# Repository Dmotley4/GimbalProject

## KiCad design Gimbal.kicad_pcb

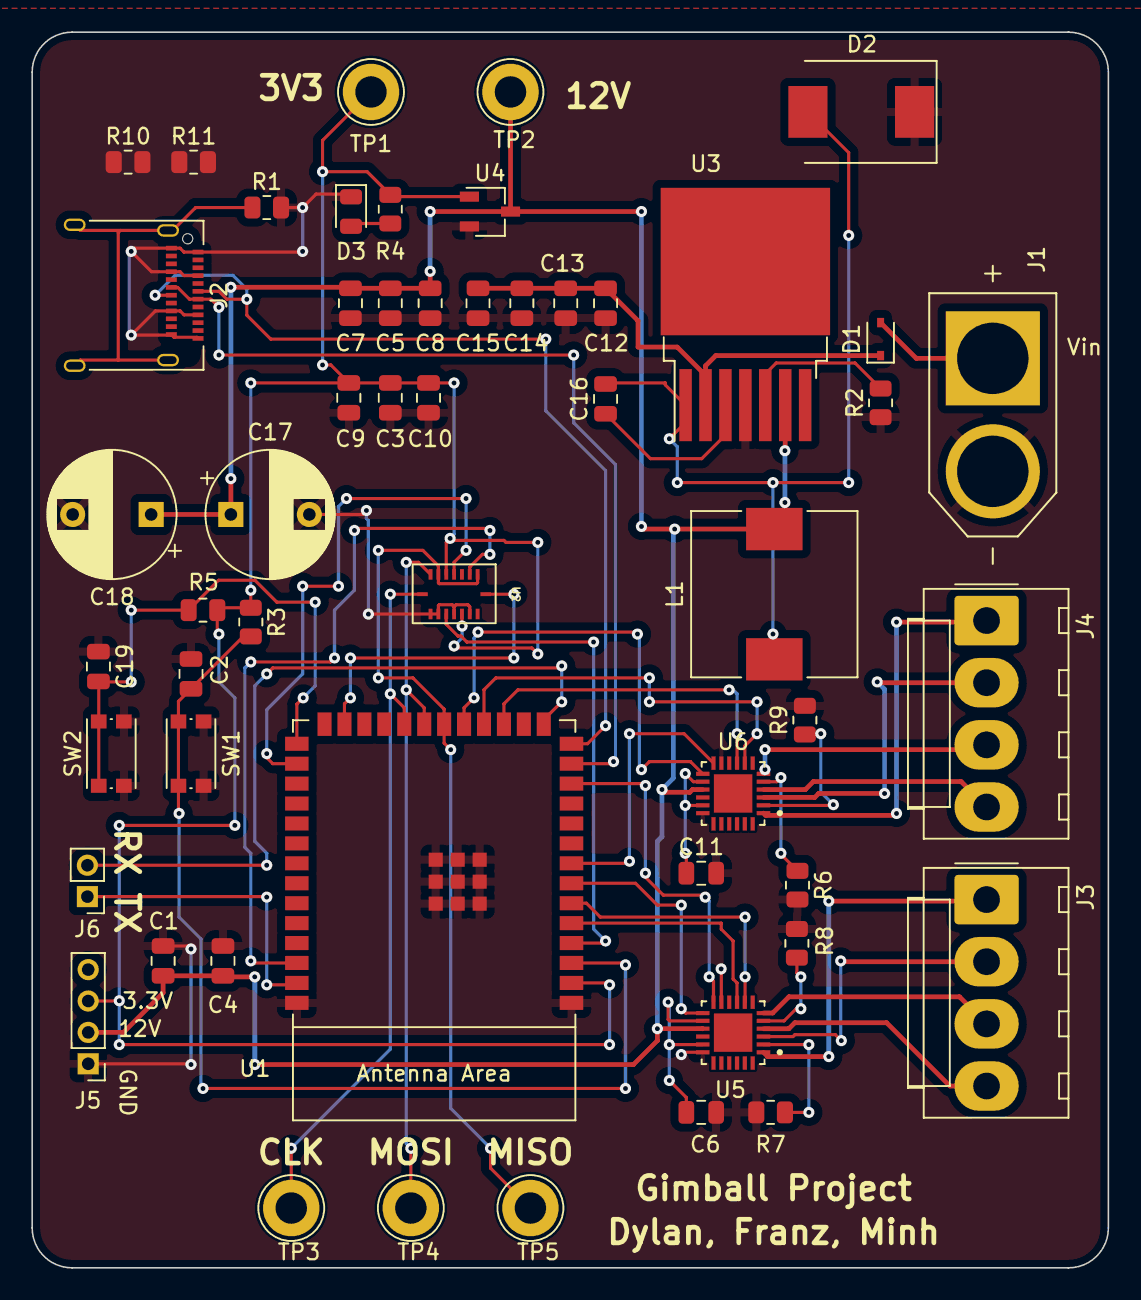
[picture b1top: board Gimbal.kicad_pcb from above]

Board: 2 copper layers, 68.6 x 78.7 mm, 53 parts (0 on the bottom side), 45 nets.

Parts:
C1, C6, C11: 22uF; C_0805_2012Metric
C2, C5, C8, C19: 0.1uF; C_0805_2012Metric
C3: 1uF; C_0805_2012Metric
C4, C7: 10uF; C_0805_2012Metric
C9, C10: 100nF; C_0805_2012Metric
C12, C13, C14: 15uF; C_0805_2012Metric
C15: 0.47 uF; C_0805_2012Metric
C16: .01uF; C_0805_2012Metric
C17, C18: 180uF; CP_Radial_D8.0mm_P5.00mm
D1: D_Schottky; D_SOD-323
D2: DIODE; D_SMC
D3: LED; LED_0805_2012Metric
J1: XT60-M; AMASS_XT60-M
J2: USB_C_Receptacle_USB2.0; USB_C_Receptacle_Amphenol_12401610E4-2A
J3, J4: 0022232041; Molex_KK-396_A-41791-0004_1x04_P3.96mm_Vertical
J5: 0022232041; PinHeader_1x04_P2.00mm_Vertical
J6: Conn_01x02; PinHeader_1x02_P2.00mm_Vertical
L1: 22uH; L_10.4x10.4_H4.8
R1, R4: 100; R_0805_2012Metric
R2: 5.6k; R_0805_2012Metric
R3, R5, R10, R11: 10k; R_0805_2012Metric
R6, R7, R8, R9: 500m; R_0805_2012Metric
SW1, SW2: SW_Push; SW_Push_1P1T_NO_CK_KMR2
TP1, TP2, TP3, TP4, TP5: TestPoint; TestPoint_Loop_D3.80mm_Drill2.0mm
U1: ESP32-S2-SOLO
U2: BMI088
U3: LM2679SX-12; TO-263-7_TabPin8
U4: TLV70433DBVT; TSOT-23
U5, U6: DRV8846RGET; QFN50P400X400X100-25N

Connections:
+3V3: C3.1, C9.1, C10.1, J5.3, R3.1, R4.1, R5.1, TP1.1, U1.2 (3V3), U2.3 (VDD), U2.11 (VDDIO), U4.1 (OUT)
+12V: C1.1, C4.1, C5.1, C7.1, C8.1, C17.1, C18.1, J5.2, L1.2, TP2.1, U3.6 (FB), U4.3 (IN), U5.15 (VM), U6.15 (VM)
+BATT: C12.1, C13.1, C14.1, C15.1, D1.1 (K), U3.2 (INPUT)
/BUCKCB: C16.1, U3.3 (CB)
/D+: J2.A6 (D+), J2.B6 (D+), U1.14 (GPIO20/U1CTS/ADC2_CH9/CLK_OUT1/USB_D+)
/D-: J2.A7 (D-), J2.B7 (D-), U1.13 (GPIO19/U1RTS/ADC2_CH8/CLK_OUT2/USB_D-)
/EN: C2.2, R3.2, SW1.1, U1.3 (EN)
/ESPIO0: C19.2, R5.2, SW2.1, U1.27 (GPIO0)
/ESPIO2: U1.38 (GPIO2/TOUCH2/ADC1_CH1), U2.14 (CSB1)
/ESPIO4: U1.4 (GPIO4/TOUCH4/ADC1_CH3), U2.5 (CSB2)
/ESPIO34: U1.25 (SPIIO5/GPIO34/FSPICS0), U2.16 (INT1)
/ESPIO35: U1.28 (SPIIO6/GPIO35/FSPID), U2.12 (INT3)
/ESPRX: J6.2, U1.15 (GPIO3/TOUCH3/ADC1_CH2)
/ESPTX: J6.1, U1.39 (GPIO1/TOUCH1/ADC1_CH0)
/Motor1Dir: U1.7 (GPIO7/TOUCH7/ADC1_CH6), U5.13 (DIR)
/Motor1M0: U1.6 (GPIO6/TOUCH6/ADC1_CH5), U5.8 (M0)
/Motor1M1: U1.5 (GPIO5/TOUCH5/ADC1_CH4), U5.9 (M1)
/Motor1Out1: J3.1, U5.1 (AOUT1)
/Motor1Out2: J3.2, U5.3 (AOUT2)
/Motor1Out3: J3.3, U5.6 (BOUT1)
/Motor1Out4: J3.4, U5.4 (BOUT2)
/Motor1Step: U1.12 (GPIO8/TOUCH8/ADC1_CH7), U5.12 (STEP)
/Motor2Dir: U1.19 (GPIO11/TOUCH11/ADC2_CH0/FSPID/FSPIIO5), U6.13 (DIR)
/Motor2M0: U1.18 (GPIO10/TOUCH10/ADC1_CH9/FSPICS0/FSPIIO4), U6.8 (M0)
/Motor2M1: U1.17 (GPIO9/TOUCH9/ADC1_CH8/FSPIHD), U6.9 (M1)
/Motor2Out1: J4.1, U6.1 (AOUT1)
/Motor2Out2: J4.2, U6.3 (AOUT2)
/Motor2Out3: J4.3, U6.6 (BOUT1)
/Motor2Out4: J4.4, U6.4 (BOUT2)
/Motor2Step: U1.8 (GPIO15/U0RTS/ADC2_CH4/XTAL_32K_P), U6.12 (STEP)
/SPI_CLK: TP3.1, U1.22 (GPIO14/TOUCH14/ADC2_CH3/FSPIWP/FSPIDQS), U2.8 (SCK)
/SPI_MISO: TP5.1, U1.20 (GPIO12/TOUCH12/ADC2_CH1/FSPICLK/FSPIIO6), U2.10 (SDO2), U2.15 (SDO1)
/SPI_MOSI: TP4.1, U1.21 (GPIO13/TOUCH13/ADC2_CH2/FSPIQ/FSPIIO7), U2.9 (SDI)
GND: C1.2, C2.1, C3.2, C4.2, C5.2, C6.2, C7.2, C8.2, C9.2, C10.2, C11.2, C12.2, C13.2, C14.2, C15.2, C17.2, C18.2, C19.1, D2.1 (A), D3.1 (K), J1.N (NEG), J2.A1 (GND), J2.A4 (VBUS), J2.A9 (VBUS), J2.A12 (GND), J2.B1 (GND), J2.B4 (VBUS), J2.B9 (VBUS), J2.B12 (GND), J5.1, R1.2, R2.1, R6.2, R7.2, R8.2, R9.2, R10.2, R11.2, SW1.2, SW2.2, U1.1 (GND), U1.40 (GND), U1.41 (GND), U2.2 (NC), U2.4 (GND), U2.6 (GNDIO), U2.7 (PS), U3.4 (GND), U4.2 (GND), U5.11 (nENBL), U5.18 (GND), U6.11 (nENBL), U6.18 (GND)
unnamed: C6.1, U5.14 (VREF), U5.17 (VINT)
unnamed: C11.1, U6.14 (VREF), U6.17 (VINT)
unnamed: C16.2, D2.2 (K), L1.1, U3.1 (SWITCH_OUTPUT)
unnamed: D1.2 (A), J1.P (POS)
unnamed: D3.2 (A), R4.2
unnamed: J2.S1 (SHIELD), R1.1
unnamed: R2.2, U3.5 (CURRENT_ADJ)
unnamed: R6.1, U6.5 (BISEN)
unnamed: R7.1, U5.2 (AISEN)
unnamed: R8.1, U5.5 (BISEN)
unnamed: R9.1, U6.2 (AISEN)

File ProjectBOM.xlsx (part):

Instructions
Fill in the cells with the YELLOW highlight. Do not edit red cells. Fill out th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 |  |  |  |  |  |  |  |  |  |  |  |  | Total Price for Project
 |  |  |  |  |  |  |  |  |  |  |  | $ | 114.16
Component | Qty (for 1 board) | Manufacturer Part # | Digi-key Part#/SKU | Other Part#/SKU | Price/unit ($) | Purchase URL | Reference Designator | Description (include component value if applicable) | Datasheet Link | Multiple | Total Qty | Total Price/part ($)
Push Button | 2.0 | KMR221NG LFS | CKN10244CT-ND |  | 0.44 | https://www.digikey.com/en/products/detail/c-k/KMR221NG-LFS/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 | SW1/SW2 | Push button switch | https://www.ckswitches.com/media/1479/kmr2.pdf | 2.0 | 1.0 | 0.88
 |  |  |  |  |  |  |  |  |  |  |  | 0
Microcontroller | 1.0 | ESP32-S2-SOLO-2-N4R2 | 1965-ESP32-S2-SOLO-2-N4R2-ND |  | 4.93 | https://www.digikey.com/en/products/detail/espressif-systems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 | U1 | ESP32 SOLO | https://www.espressif.com/sites/default/files/documentation/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 | 0.0 | 1.0 | 0
IMU | 1.0 | BMI088 | 828-1082-1-ND |  | 10.7 | https://www.digikey.com/en/products/detail/bosch-sensortec/B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 | U2 | Bosch IMU | https://www.bosch-sensortec.com/media/boschsensortec/downloa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 | 1.0 | 1.0 | 10.7
12V Buck Converter | 1.0 | LM2679SX-12 | LM2679SX-12/NOPBCT-ND |  | 6.97 | https://www.digikey.com/en/products/detail/texas-instruments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 | U3 | 12 v Buck | https://www.ti.com/lit/gpn/lm2679 | 1.0 | 1.0 | 6.97
LDO | 1.0 | TLV70433DBVT | 296-27946-1-ND |  | 1.3 | https://www.digikey.com/en/products/detail/texas-instruments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 | U4 | Voltage Regulator | https://www.ti.com/general/docs/suppproductinfo.tsp?distId=1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 | 1.0 | 1.0 | 1.3
H-Bridge/Motor Controller IC | 2.0 | DRV8846RGET | 296-37986-1-ND |  | 3.41 | https://www.digikey.com/en/products/detail/texas-instruments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 | U5/U6 | H-Bridge/Motor Controller IC | https://www.ti.com/general/docs/suppproductinfo.tsp?distId=1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 | 2.0 | 2.0 | 6.82
 |  |  |  |  |  |  |  |  |  |  |  | 0
Stepper Motor | 2.0 |  |  | STEPPERONLINE/Amazon | 11.99 | https://www.amazon.com/STEPPERONLINE-Bipolar-Stepper-22-6oz-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 | NOT ON BOARD | Neema 17 short body | https://www.omc-stepperonline.com/download/17HS08-1004S.pdf | 2.0 | 2.0 | 23.98
Motor Connector | 3.0 | Molex 207778-0004 | Molex | 538-207778-0004 | 7.45 | https://www.mouser.com/ProductDetail/Molex/207778-0004?qs=%2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 | NOT ON BOARD | Molex connectors | https://www.mouser.com/datasheet/2/276/1/2077780004_CRIMP_HO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 | 1.0 | 3.0 | 7.45
Battery Holder | 1.0 | 18650 Battery Holder (4 slot) |  |  | 1.79 | https://www.amazon.com/Battery-Holder-Li-Ion-Envistia-Mall/d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 | NOT ON BOARD | 4 slot battery holder |  | 1.0 | 1.0 | 1.79
18650 LiPo Battery | 1.0 |  | 18650 LiPo Battery | DQGG 4-Pack 3.7v 18650 | 19.99 | https://www.amazon.com/Rechargeable-Batteries-Flashlight-Doo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 | NOT ON BOARD | 18650 LiPo Battery |  | 1.0 | 1.0 | 19.99
 |  |  |  |  |  |  |  |  |  |  |  | 0
USB C Receptacle | 1.0 | USB4125-GF-A | 2073-USB4125-GF-ACT-ND |  | 1.63 | https://www.digikey.com/en/products/detail/amphenol-cs-comme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 | J2 | USC_C connector receptacle | https://gct.co/files/drawings/usb4125.pdf?v=175f672b-2b35-4f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 | 1.0 | 1.0 | 1.63
Female Headers 4pt | 2.0 | PPPC041LFBN-RC | S7037-ND |  | 0.47 | https://www.digikey.com/en/products/detail/sullins-connector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 | J3/J4 | 4 pin female header | https://media.digikey.com/pdf/Data%20Sheets/Sullins%20PDFs/F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 | 2.0 | 2.0 | 0.94
xt60 | 1.0 | PRT-10474 |  | 474-PRT-10474 | 1.5 | https://www.mouser.com/ProductDetail/SparkFun/PRT-10474?qs=W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 | J1 | xt60 connector/motor connector | https://www.mouser.com/datasheet/2/813/xt60-2490175.pdf | 1.0 | 1.0 | 1.5
Male Header | 1.0 | 2PH1-08-UA | 2057-2PH1-08-UA-ND |  | 0.26 | https://www.digikey.com/en/products/detail/adam-tech/2PH1-08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 | J5/J6 | 8 pin strip | https://app.adam-tech.com/products/download/data_sheet/20045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 | 1.0 | 1.0 | 0.26
 |  |  |  |  |  |  |  |  |  |  |  | 0
15 uF Capacitor | 3.0 | C2012X5R1V156M125AC | 445-14423-1-ND |  | 4.6 | https://www.digikey.com/en/products/detail/tdk-corporation/C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 | C12/C13/C14 |  | https://product.tdk.com/system/files/dam/doc/product/capacit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 | 1.0 | 10.0 | 4.6
22uF Capacitor | 1.0 | CL21A226MQQNNNG | 1276-6460-1-ND |  | 0.93 | https://www.digikey.com/en/products/detail/samsung-electro-m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 | C1 | 22 uF Capacitor | https://media.digikey.com/pdf/Data%20Sheets/Samsung%20PDFs/C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 | 1.0 | 10.0 | 0.93
1uF Capacitor | 1.0 | CL21B105KAFNNNE | 1276-1066-1-ND |  | 0.65 | https://www.digikey.com/en/products/detail/samsung-electro-m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 | C3 | 1uF Capacitor | https://media.digikey.com/pdf/Data%20Sheets/Samsung%20PDFs/C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 | 1.0 | 10.0 | 0.65
10uF Capacitor | 2.0 | CL21A106KOQNNNE | 1276-1096-1-ND |  | 0.74 | https://www.digikey.com/en/products/detail/samsung-electro-m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 | C4/C7 | 10 uF Capacitor | https://media.digikey.com/pdf/Data%20Sheets/Samsung%20PDFs/C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 | 1.0 | 10.0 | 0.74
100nF Capacitor | 2.0 | CL21B104KBFWPNE | 1276-6506-1-ND |  | 1.21 | https://www.digikey.com/en/products/detail/samsung-electro-m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 | C9/C10 | CL21B104KBFWPNE | http://www.samsungsem.com/kr/support/product-search/mlcc/CL2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 | 1.0 | 10.0 | 1.21
.1uF Capacitor | 4.0 | CL21B104KACNNNC | 1276-1099-1-ND |  | 0.37 | https://www.digikey.com/en/products/detail/samsung-electro-m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 | C2/C5/C8/C19 | 0.1 uF Capacitor | https://media.digikey.com/pdf/Data%20Sheets/Samsung%20PDFs/C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 | 1.0 | 10.0 | 0.37
22uF Capacitor | 2.0 | CL21A226MQQNNNG | 1276-6460-1-ND |  | 0.93 | https://www.digikey.com/en/products/detail/samsung-electro-m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 | C6/C11 | 22 uF Capacitor | https://media.digikey.com/pdf/Data%20Sheets/Samsung%20PDFs/C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 | 1.0 | 10.0 | 0.93
.01 uF Capacitor | 1.0 | CGA4J2X8R1H104K125AA | 445-5909-1-ND |  | 1.21 | https://www.digikey.com/en/products/detail/tdk-corporation/C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 | C16 |  | https://product.tdk.com/en/system/files?file=dam/doc/product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 | 1.0 | 10.0 | 1.21
180 uF Capacitor | 2.0 | EEU-FR1V181B | P15385CT-ND |  | 4.48 | https://www.digikey.com/en/products/detail/panasonic-electro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 | C17/C18 |  | https://industrial.panasonic.com/cdbs/www-data/pdf/RDF0000/A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 | 1.0 | 10.0 | 4.48
0.47 uF Capacitor | 1.0 | CL21B474KBFNFNE | 1276-2966-1-ND |  | 0.77 | https://www.digikey.com/en/products/detail/samsung-electro-m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 | C15 |  | http://www.samsungsem.com/kr/support/product-search/mlcc/CL2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 | 1.0 | 10.0 | 0.77
 |  |  |  | Mouser# |  |  |  |  |  |  |  | 0
100 Resistor | 2.0 | CRGS0805J100R | A129233CT-ND |  | 0.45 | https://www.digikey.com/en/products/detail/te-connectivity-a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 | R1/R4 | 100 Ohm Resistor | https://www.te.com/commerce/DocumentDelivery/DDEController?A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 | 4.0 | 2.0 | 1.8
500m Resistor | 4.0 | RL1220S-R50-F | RL12S.50FCT-ND |  | 2.45 | https://www.digikey.com/en/products/detail/susumu/RL1220S-R5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 | R/6R7/R8/R9 | 500 mOhm Resistor | https://www.susumu.co.jp/common/pdf/n_catalog_partition08_en.pdf | 1.0 | 10.0 | 2.45
10k Resistor | 2.0 | RMCF0805JT10K0 | RMCF0805JT10K0CT-ND |  | 0.18 | https://www.digikey.com/en/products/detail/stackpole-electro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 | R5/R3 | 10k Ohm Resistor | https://www.seielect.com/catalog/sei-rmcf_rmcp.pdf | 1.0 | 10.0 | 0.18
5.6k Resistor | 1.0 | RMCF0805FT5K60 | MCF0805FT5K60CT-ND |  | 0.24 | https://www.digikey.com/en/products/detail/stackpole-electro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 | R2 | 5.6k Ohm Resistor | https://www.seielect.com/catalog/sei-rmcf_rmcp.pdf | 1.0 | 10.0 | 0.24
 |  |  |  |  |  |  |  |  |  |  |  | 0
LED | 1.0 | HSMQ-C170 | 516-3071-1-ND |  | 1.17 | https://www.digikey.com/en/products/detail/broadcom-limited/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 | D3 | led indicator light | https://docs.broadcom.com/docs/AV02-0977EN | 2.0 | 1.0 | 2.34
Schottky Diode | 1.0 | B0520WS-7-F | B0520WS-FDICT-ND |  | 0.37 | https://www.digikey.com/en/products/detail/diodes-incorporat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 | D1 | Schottky Diode for battery connector | https://www.diodes.com/assets/Datasheets/ds30235.pdf | 2.0 | 1.0 | 0.74
Diode | 1.0 | VS-6TQ045S-M3 | 112-VS-6TQ045S-M3-ND |  | 1.19 | https://www.digikey.com/en/products/detail/vishay-general-se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 | D2 | Diode for Buck Converter | https://www.vishay.com/docs/94945/vs-6tqs-m3.pdf | 2.0 | 1.0 | 2.38
 |  |  |  |  |  |  |  |  |  |  |  | 0
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
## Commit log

2022-10-22 fixed boot pin
2022-10-25 finished erc check
2022-10-25 filled in schematic
2022-10-25 draft submission
2022-11-03 changed esp to solo s2
2022-11-03 assigned all footprints
2022-11-03 preliminary layout
2022-11-03 prelim routing
2022-11-04 routing actually good
2022-11-04 new schematic
2022-11-04 started new layout
2022-11-10 New layout
2022-11-10 fixing schematic erc issues and adding test points
2022-11-11 schematic changes
2022-11-11 updated layout and schematic to fix errors
2022-11-11 Changed numbering
2022-11-11 layout completed
2022-11-11 comment
2022-11-11 Fixed USB connector issues
